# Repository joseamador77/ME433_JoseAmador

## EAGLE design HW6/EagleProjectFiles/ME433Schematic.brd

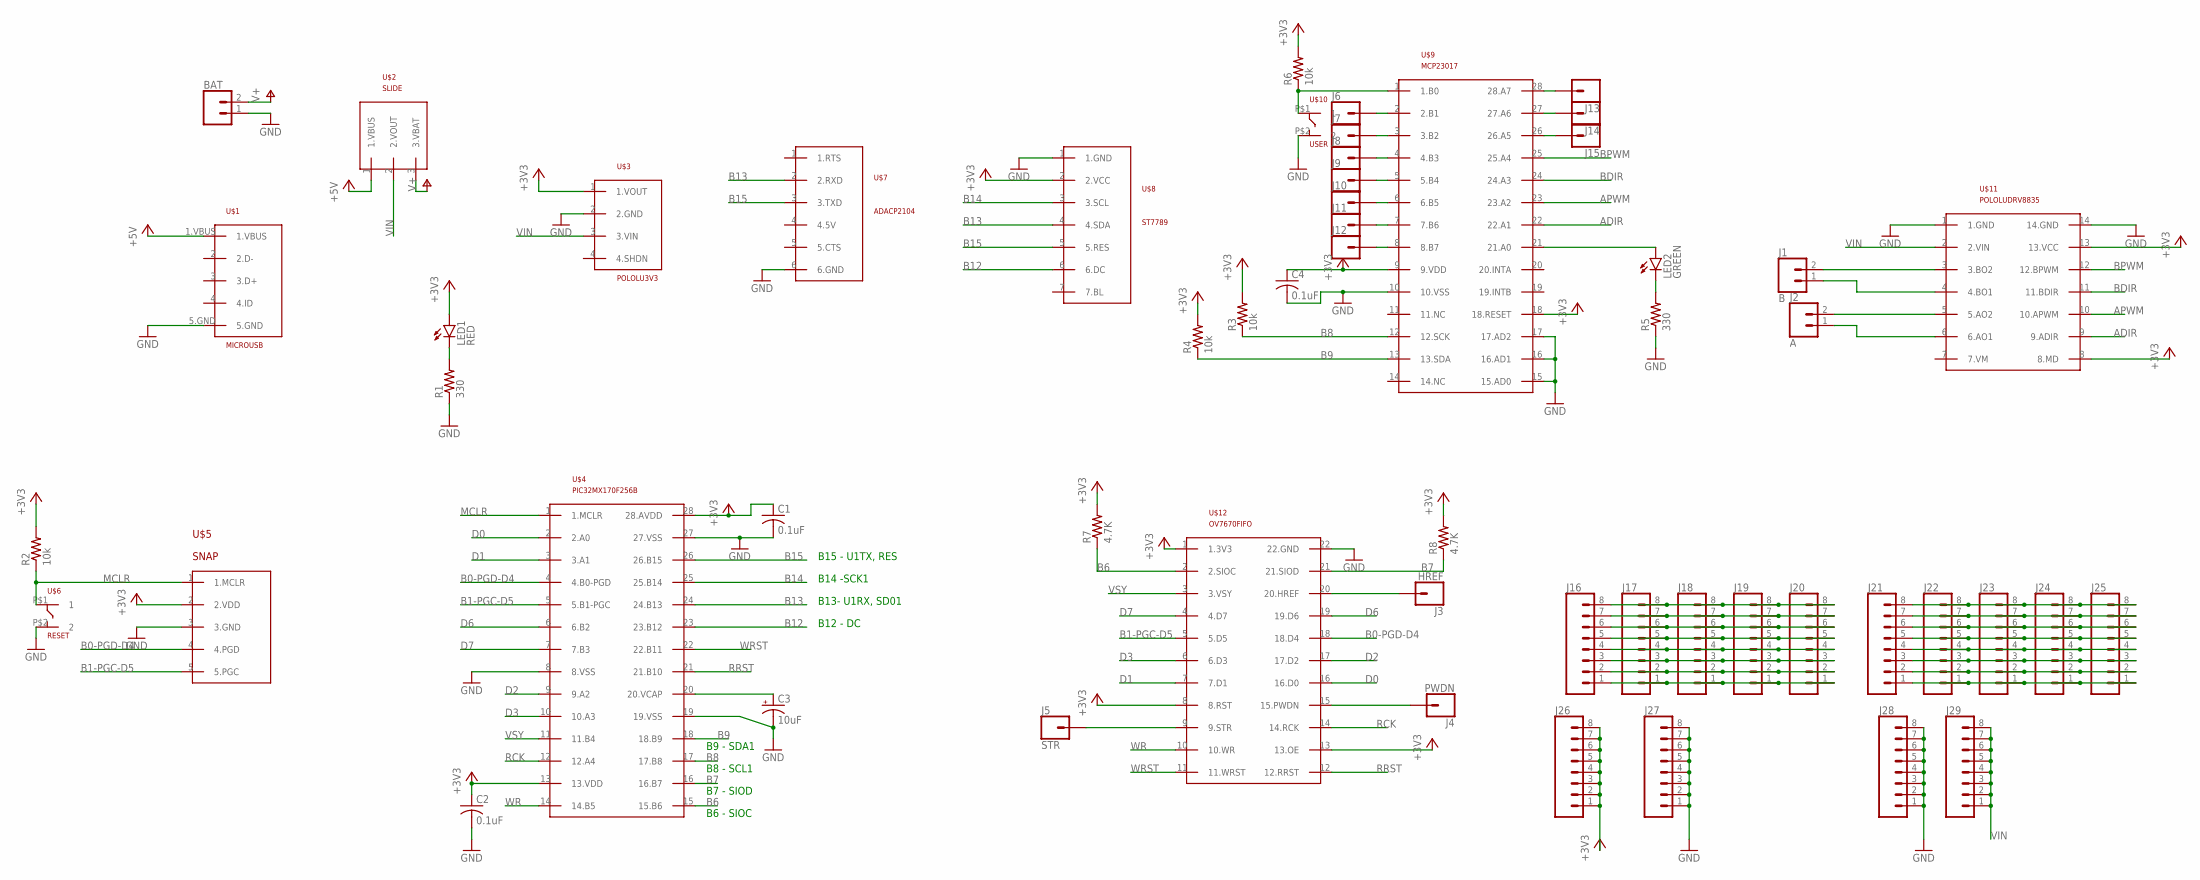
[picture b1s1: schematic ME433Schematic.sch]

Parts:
BAT: CONN_02; 1X02
C1, C2, C4: 0.1uF; C025-030X050
C3: 10uF; B45181B
J1: B; 1X02
J2: A; 1X02
J3: HREF; 1X01
J4: PWDN; 1X01
J5: STR; 1X01
J6, J7, J8, J9, J10, J11, J12, J13, J14, J15: CONN_01; 1X01
J16, J17, J18, J19, J20, J21, J22, J23, J24, J25, J26, J27, J28, J29: CONN_08"; 1X08
LED1: RED; LED3MM
LED2: GREEN; LED3MM
R1, R5: 330; 0207/10
R2, R3, R4, R6: 10k; 0207/10
R7, R8: 4.7K; 0207/10
U$1: MICROUSB
U$2: SLIDE
U$3: POLOLU3V3
U$4: PIC32MX170F256B; DIL28-3
U$5: SNAP
U$6: RESET; PUSH
U$7: ADACP2104
U$8: ST7789
U$9: MCP23017; DIL28-3
U$10: USER; PUSH
U$11: POLOLUDRV8835
U$12: OV7670FIFO

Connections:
+3V3: C1.1, C2.1, C4.1, J26.1, J26.2, J26.3, J26.4, J26.5, J26.6, J26.7, J26.8, LED1.A, R2.2, R3.2, R4.2, R6.2, R7.2, R8.2, U$3.1 (1.VOUT), U$4.13 (13.VDD), U$4.28 (28.AVDD), U$5.2 (2.VDD), U$8.2 (2.VCC), U$9.9 (9.VDD), U$9.18 (18.RESET), U$11.8 (8.MD), U$11.13 (13.VCC), U$12.1 (1.3V3), U$12.8 (8.RST), U$12.13 (13.OE)
+5V: U$1.1.VBUS, U$2.1 (1.VBUS)
ADIR: U$9.22 (22.A1), U$11.9 (9.ADIR)
APWM: U$9.23 (23.A2), U$11.10 (10.APWM)
B0-PGD-D4: U$4.4 (4.B0-PGD), U$5.4 (4.PGD), U$12.18 (18.D4)
B1-PGC-D5: U$4.5 (5.B1-PGC), U$5.5 (5.PGC), U$12.5 (5.D5)
B6: R7.1, U$4.15 (15.B6), U$12.2 (2.SIOC)
B7: R8.1, U$4.16 (16.B7), U$12.21 (21.SIOD)
B8: R3.1, U$4.17 (17.B8), U$9.12 (12.SCK)
B9: R4.1, U$4.18 (18.B9), U$9.13 (13.SDA)
B12: U$4.23 (23.B12), U$8.6 (6.DC)
B13: U$4.24 (24.B13), U$7.2 (2.RXD), U$8.4 (4.SDA)
B14: U$4.25 (25.B14), U$8.3 (3.SCL)
B15: U$4.26 (26.B15), U$7.3 (3.TXD), U$8.5 (5.RES)
BDIR: U$9.24 (24.A3), U$11.11 (11.BDIR)
BPWM: U$9.25 (25.A4), U$11.12 (12.BPWM)
D0: U$4.2 (2.A0), U$12.16 (16.D0)
D1: U$4.3 (3.A1), U$12.7 (7.D1)
D2: U$4.9 (9.A2), U$12.17 (17.D2)
D3: U$4.10 (10.A3), U$12.6 (6.D3)
D6: U$4.6 (6.B2), U$12.19 (19.D6)
D7: U$4.7 (7.B3), U$12.4 (4.D7)
GND: BAT.1, C1.2, C2.2, C3.-, C4.2, J27.1, J27.2, J27.3, J27.4, J27.5, J27.6, J27.7, J27.8, J28.1, J28.2, J28.3, J28.4, J28.5, J28.6, J28.7, J28.8, R1.1, R5.1, U$1.5.GND, U$3.2 (2.GND), U$4.8 (8.VSS), U$4.19 (19.VSS), U$4.27 (27.VSS), U$5.3 (3.GND), U$6.P$2 (2), U$7.6 (6.GND), U$8.1 (1.GND), U$9.10 (10.VSS), U$9.15 (15.AD0), U$9.16 (16.AD1), U$9.17 (17.AD2), U$10.P$2 (2), U$11.1 (1.GND), U$11.14 (14.GND), U$12.22 (22.GND)
MCLR: R2.1, U$4.1 (1.MCLR), U$5.1 (1.MCLR), U$6.P$1 (1)
unnamed: LED1.K (C), R1.2
unnamed: C3.+, U$4.20 (20.VCAP)
unnamed: LED2.A, U$9.21 (21.A0)
unnamed: J5.1, U$12.9 (9.STR)
unnamed: R6.1, U$9.1 (1.B0), U$10.P$1 (1)
unnamed: LED2.K (C), R5.2
unnamed: J1.2, U$11.3 (3.BO2)
unnamed: J1.1, U$11.4 (4.BO1)
unnamed: J2.2, U$11.5 (5.AO2)
unnamed: J2.1, U$11.6 (6.AO1)
unnamed: J4.1, U$12.15 (15.PWDN)
unnamed: J3.1, U$12.20 (20.HREF)
unnamed: J6.1, U$9.2 (2.B1)
unnamed: J7.1, U$9.3 (3.B2)
unnamed: J8.1, U$9.4 (4.B3)
unnamed: J9.1, U$9.5 (5.B4)
unnamed: J10.1, U$9.6 (6.B5)
unnamed: J11.1, U$9.7 (7.B6)
unnamed: J12.1, U$9.8 (8.B7)
unnamed: J13.1, U$9.28 (28.A7)
unnamed: J14.1, U$9.27 (27.A6)
unnamed: J15.1, U$9.26 (26.A5)
unnamed: J16.8, J17.8, J18.8, J19.8, J20.8
unnamed: J16.7, J17.7, J18.7, J19.7, J20.7
unnamed: J16.6, J17.6, J18.6, J19.6, J20.6
unnamed: J16.5, J17.5, J18.5, J19.5, J20.5
unnamed: J16.4, J17.4, J18.4, J19.4, J20.4
unnamed: J16.3, J17.3, J18.3, J19.3, J20.3
unnamed: J16.2, J17.2, J18.2, J19.2, J20.2
unnamed: J16.1, J17.1, J18.1, J19.1, J20.1
unnamed: J21.8, J22.8, J23.8, J24.8, J25.8
unnamed: J21.7, J22.7, J23.7, J24.7, J25.7
unnamed: J21.6, J22.6, J23.6, J24.6, J25.6
unnamed: J21.5, J22.5, J23.5, J24.5, J25.5
unnamed: J21.4, J22.4, J23.4, J24.4, J25.4
unnamed: J21.3, J22.3, J23.3, J24.3, J25.3
unnamed: J21.2, J22.2, J23.2, J24.2, J25.2
unnamed: J21.1, J22.1, J23.1, J24.1, J25.1
RCK: U$4.12 (12.A4), U$12.14 (14.RCK)
RRST: U$4.21 (21.B10), U$12.12 (12.RRST)
V+: BAT.2, U$2.3 (3.VBAT)
VIN: J29.1, J29.2, J29.3, J29.4, J29.5, J29.6, J29.7, J29.8, U$2.2 (2.VOUT), U$3.3 (3.VIN), U$11.2 (2.VIN)
VSY: U$4.11 (11.B4), U$12.3 (3.VSY)
WR: U$4.14 (14.B5), U$12.10 (10.WR)
WRST: U$4.22 (22.B11), U$12.11 (11.WRST)

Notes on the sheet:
B15 - U1TX, RES
B13- U1RX, SD01
B14 -SCK1
B12 - DC
B9 - SDA1
B8 - SCL1
B7 - SIOD
B6 - SIOC

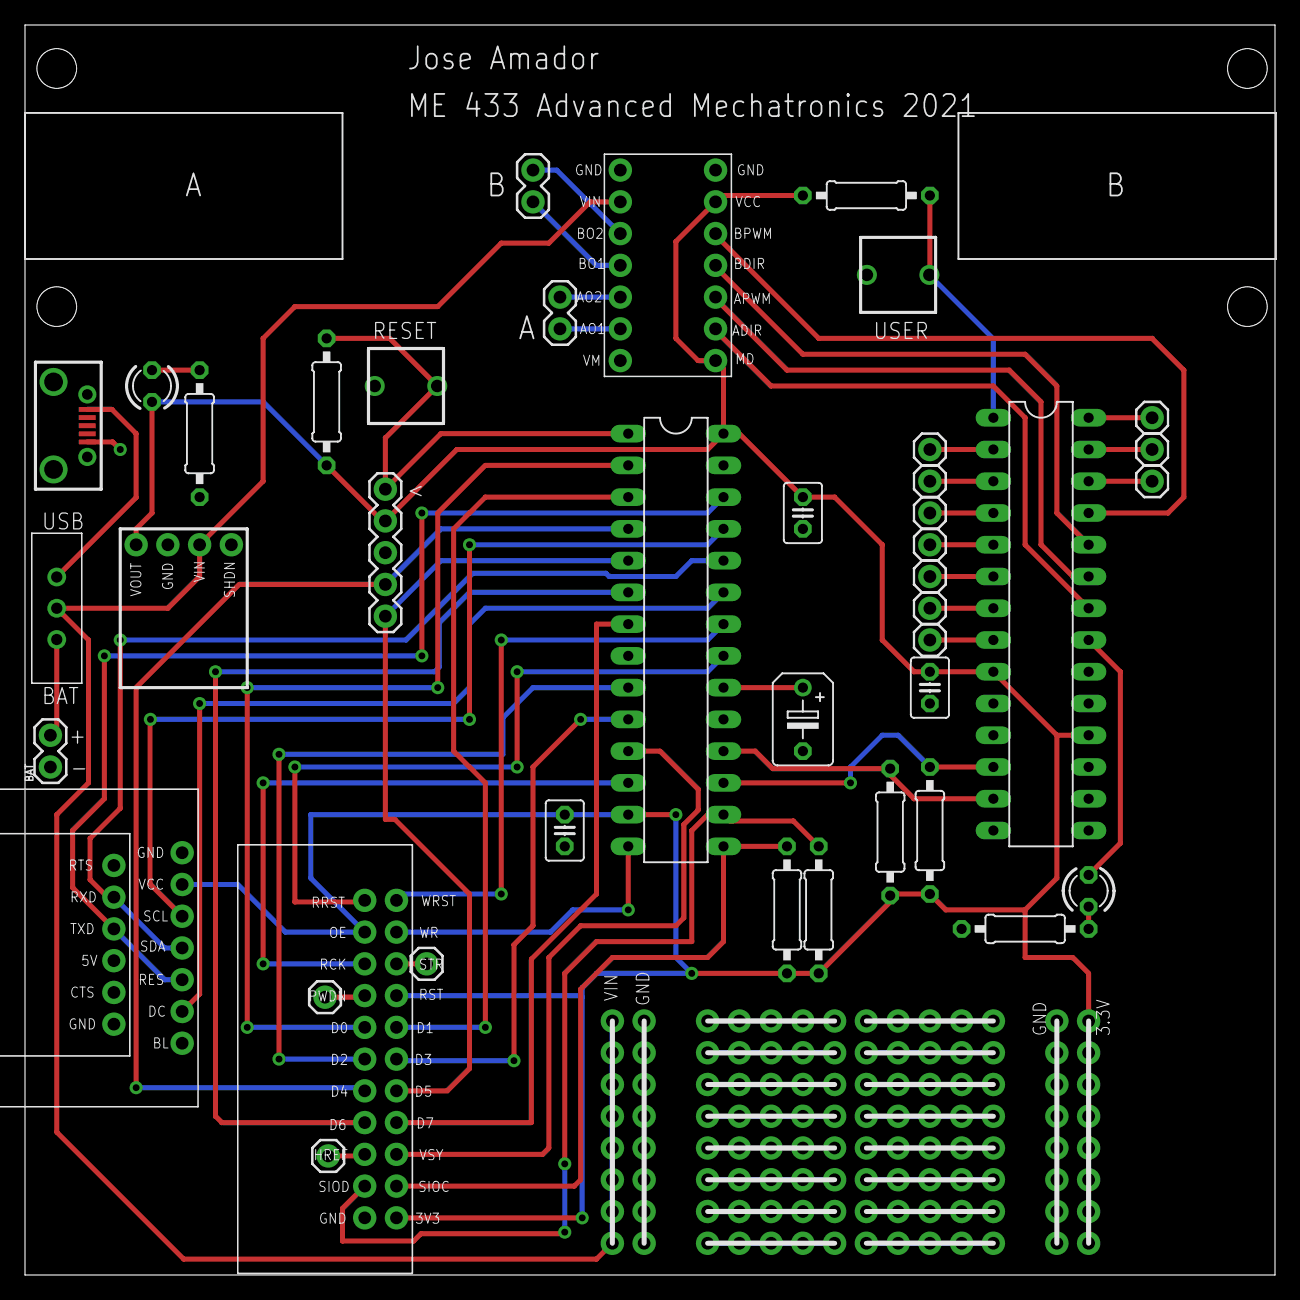
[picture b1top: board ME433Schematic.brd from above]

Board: 2 copper layers, 100.0 x 100.0 mm, 56 parts (0 on the bottom side), 69 nets.

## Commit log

2021-04-11 All done
    finished assignment
2021-04-11 changed nameof pdf
2021-04-18 Completed hw4
2021-04-26 HW5 Done
    finished UARt
2021-04-26 changed folders
2021-04-29 FinishedHW7
2021-05-06 Finished HW8
2021-05-13 FinishedHW10
    Finished LEDs
2021-05-30 Finished HW9
    all done
2021-06-08 Finished HW6
    also worked on HW11
2021-06-08 Finished HW11
2021-06-12 FinishedHW16
    yeehaw
